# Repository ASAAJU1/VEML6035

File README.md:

# VEML6035 Module for use with the arduino 
# Design by BALOGUN TOBILOBA ODUNAYO
# <a>www.hyperedge.tech</a>
VEML6035 is a 16-bit low power, high sensitivity CMOS
ambient light sensor operated via a simple I2C command.
The sensor offers an active interruption feature that is
triggered outside of the threshold window settings
eliminating loading on the host. Active average power
consumption is around 300 μW.
VEML6035 incorporates a photodiode, amplifiers, and
analog / digital circuits in a single chip. Vishay’s patented
FiltronTM technology, a wafer level optical filter, provides
the best spectral sensitivity to match human eye responses.
The sensor has excellent temperature compensation to
maintain output stability under changing temperature and its
refresh rate setting does not need an external RC low pass
filter. There is a programmable shutdown mode which
reduces current consumption to 0.5 μA. Operating voltage
ranges from 1.7 V to 3.6 V.

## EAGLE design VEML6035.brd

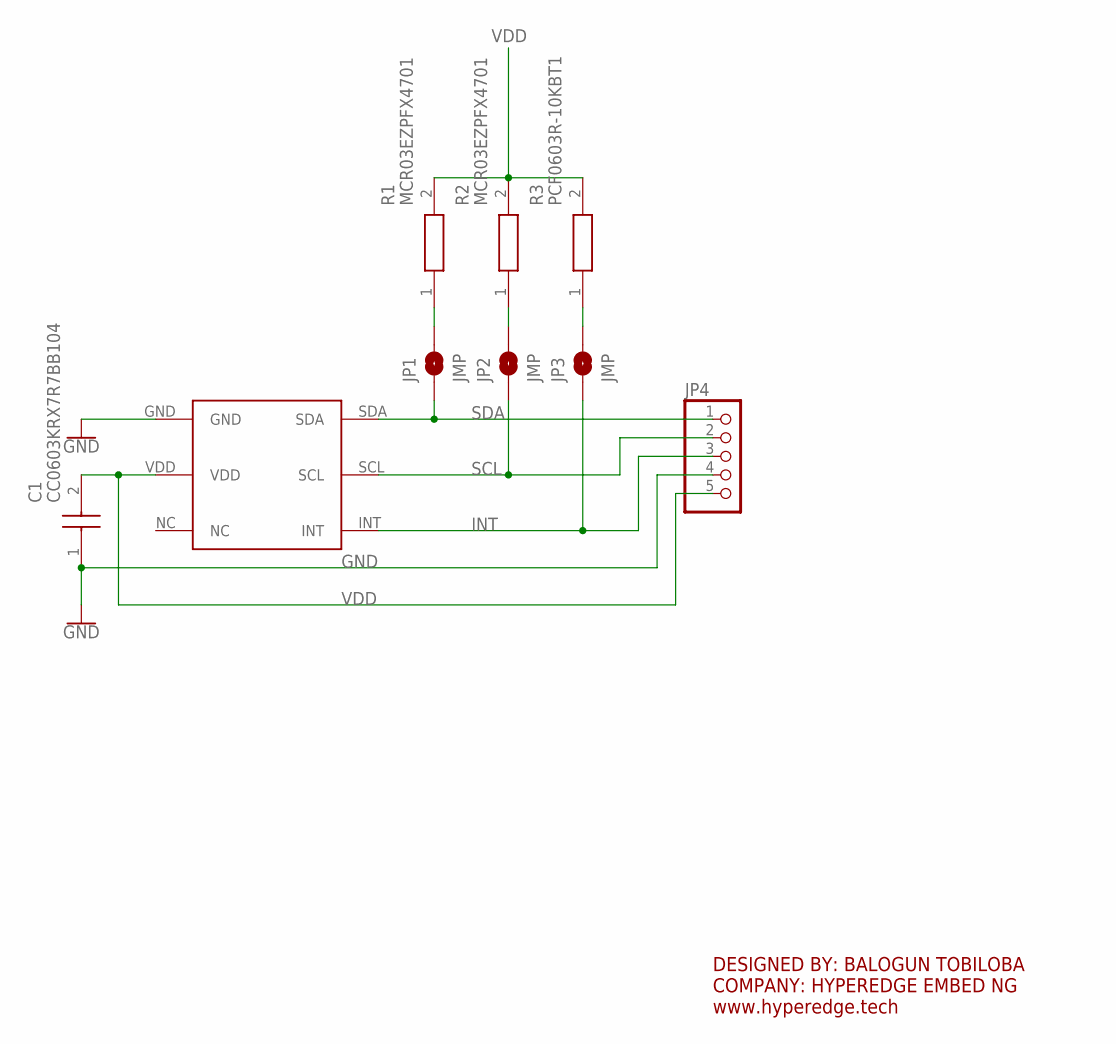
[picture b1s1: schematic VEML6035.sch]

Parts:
C1: CC0603KRX7R7BB104; CAPC1608X90N
JP1, JP2, JP3: JMP; SMT-JUMPER_2_NO_NO-SILK
JP4: PINHD-1X5; 1X05
R1, R2: MCR03EZPFX4701; RESC1608X55N
R3: PCF0603R-10KBT1; RESC1608X65N
U$1: VEML6035

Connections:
GND: C1.1 (C1), JP4.4, U$1.GND
INT: JP3.1, JP4.3, U$1.INT
unnamed: JP1.2, R1.1
unnamed: JP2.2, R2.1
unnamed: JP3.2, R3.1
SCL: JP2.1, JP4.2, U$1.SCL
SDA: JP1.1, JP4.1, U$1.SDA
VDD: C1.2 (C2), JP4.5, R1.2, R2.2, R3.2, U$1.VDD

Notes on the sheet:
DESIGNED BY: BALOGUN TOBILOBA COMPANY: HYPEREDGE EMBED NG www.hyperedge.tech

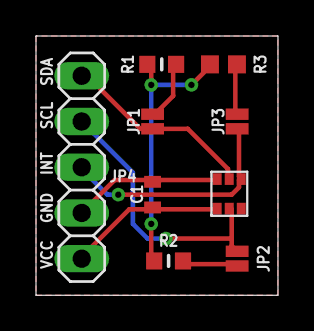
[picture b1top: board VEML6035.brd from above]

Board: 2 copper layers, 13.4 x 14.4 mm, 9 parts (0 on the bottom side), 8 nets.
